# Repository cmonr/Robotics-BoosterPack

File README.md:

Robotics-BoosterPack
====================

Robotics BoosterPack for the Tiva Launchpad

For lack of a better place, the Mouser BoM: 
[Mouser BoM](http://www.mouser.com/ProjectManager/ProjectDetail.aspx?AccessID=04738dc8be)

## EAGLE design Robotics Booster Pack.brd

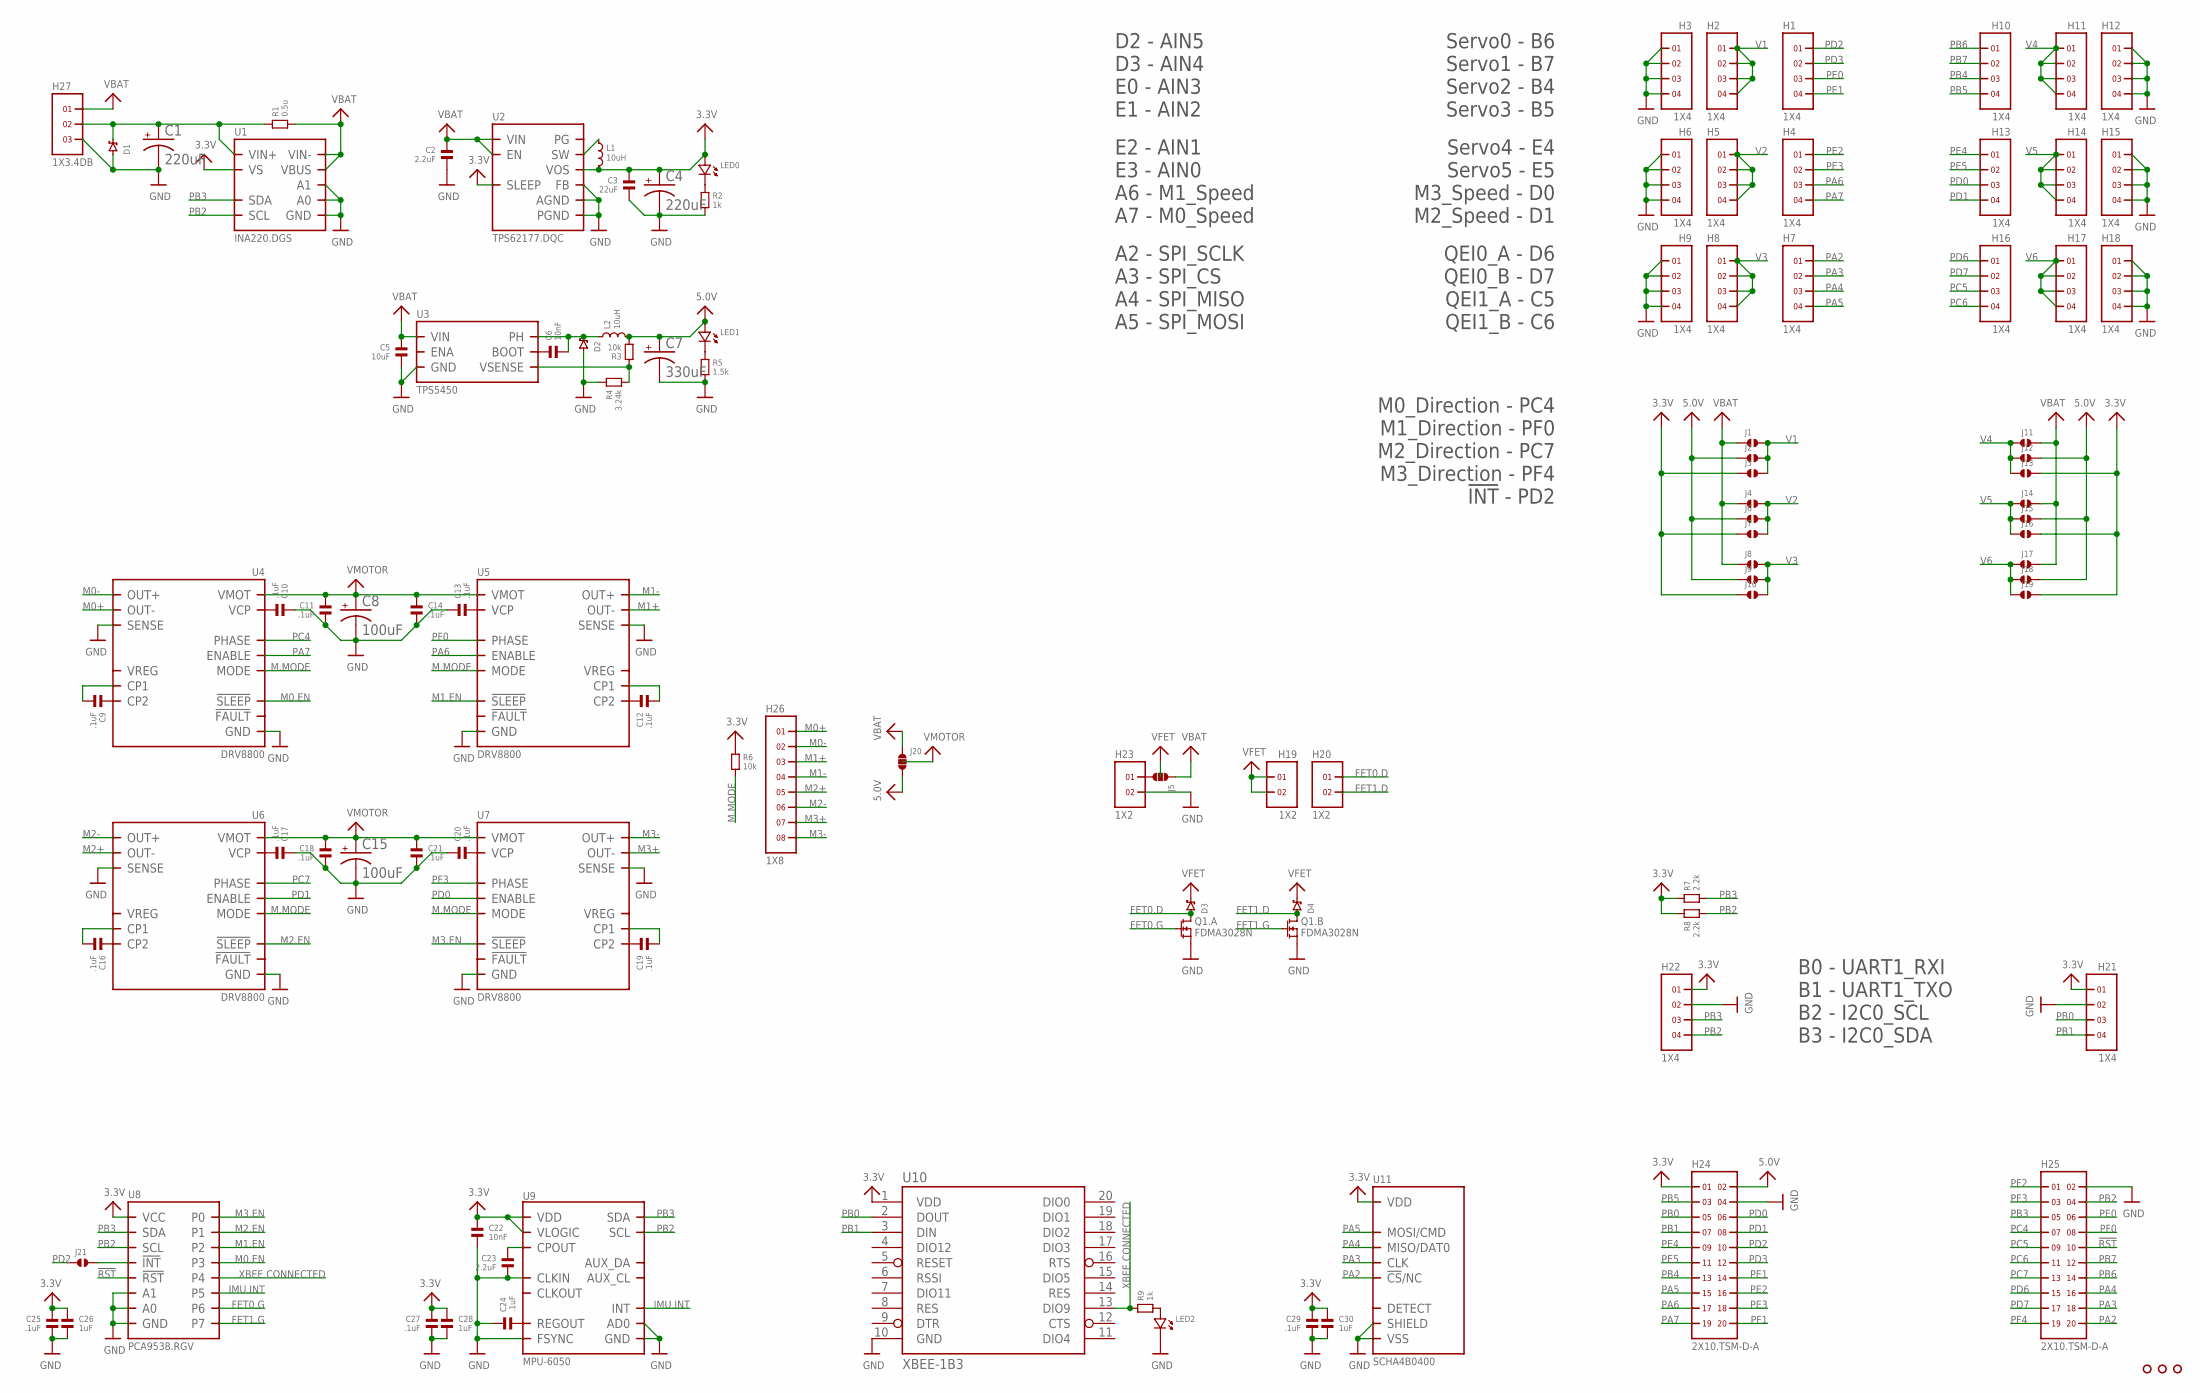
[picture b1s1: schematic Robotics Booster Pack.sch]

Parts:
C1, C4: 220uF; PANASONIC_E
C2, C23: 2.2uF; 0603
C3: 22uF; 0805
C5: 10uF; 1206
C6, C22: 10nF; 0603
C7: 330uF; PANASONIC_E
C8, C15: 100uF; PANASONIC_E
C9, C10, C11, C12, C13, C14, C16, C17, C18, C19, C20, C21, C24, C25, C27, C29: .1uF; 0603
C26, C28, C30: 1uF; 0603
D1, D3, D4: CDBMT2100-HF; SOD-123H
D2: CDBC5XXX-G; DO-214AB
H1, H2, H3, H4, H5, H6, H7, H8, H9, H10, H11, H12, H13, H14, H15, H16, H17, H18, H21, H22: 1X4
H19, H20, H23: 1X2
H24, H25: 2X10.TSM-D-A; TSM-110-XX-XXX-DV-A
H26: 1X8; 1824480000
H27: 1X3.4DB; 4DB-P108-02
J1, J2, J4, J6, J8, J9, J11, J13, J14, J15, J17, J18, J21: SOLDERJUMPER.2.LRG; 2.LRG
J3, J7, J10, J12, J16, J19: SOLDERJUMPER.2.LRG.PASTE; 2.LRG.PASTE
J5, J20: SOLDERJUMPER.3.LRG.12; 3.LRG.12
L1: 10uH; SRN6045
L2: 10uH; XAL6060
LED0, LED1, LED2: LED.0603; 0603.LED
Q1: FDMA3028N; MICROFET.2X2
R1: 0.5u; 2512
R2, R9: 1k; 0603
R3, R6: 10k; 0603
R4: 3.24k; 0603
R5: 1.5k; 0603
R7, R8: 2.2k; 0603
U1: INA220.DGS; DGS.10
U2: TPS62177.DQC; DQC
U3: TPS5450; DDA
U4, U5, U6, U7: DRV8800; RTY.16
U8: PCA9538.RGV; RGV.16
U9: MPU-6050; QFN.24.4X4
U10: XBEE-1B3; XBEE-SMD
U11: SCHA4B0400
U$3, U$4, U$21: HOLE.4MM; #4

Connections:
3.3V: C3.1, C4.+, C22.1, C25.1, C26.1, C27.1, C28.1, C29.1, C30.1, H21.1, H22.1, H24.1, J3.1, J7.1, J10.1, J13.1, J16.1, J19.1, L1.2, LED0.P$1 (1), R6.1, R7.1, R8.1, U1.6 (VS), U2.8 (SLEEP), U2.10 (VOS), U8.14 (VCC), U9.8 (VLOGIC), U9.13 (VDD), U10.1 (VDD), U11.VDD
5.0V: C7.+, H24.2, J2.1, J6.1, J9.1, J12.1, J15.1, J18.1, J20.3, L2.2, LED1.P$1 (1), R3.2
!RST: H25.10, U8.1 (!RST)
FET0.D: D3.2, H20.1, Q1.6 (D), Q1.PAD@1 (D)
FET0.G: Q1.2 (G), U8.9 (P6)
FET1.D: D4.2, H20.2, Q1.3 (D), Q1.PAD@2 (D)
FET1.G: Q1.5 (G), U8.10 (P7)
GND: C1.-, C2.2, C3.2, C4.-, C5.2, C7.-, C8.-, C10.1, C11.2, C13.1, C14.2, C15.-, C17.1, C18.2, C20.1, C21.2, C22.2, C23.2, C24.1, C25.2, C26.2, C27.2, C28.2, C29.2, C30.2, D1.2, D2.2, H3.1, H3.2, H3.3, H3.4, H6.1, H6.2, H6.3, H6.4, H9.1, H9.2, H9.3, H9.4, H12.1, H12.2, H12.3, H12.4, H15.1, H15.2, H15.3, H15.4, H18.1, H18.2, H18.3, H18.4, H21.2, H22.2, H23.2, H24.4, H25.2, H27.3, LED2.P$2 (2), Q1.1 (S), Q1.4 (S), R2.2, R4.1, R5.2, U1.1 (A1), U1.2 (A0), U1.7 (GND), U2.1 (PGND), U2.5 (FB), U2.6 (AGND), U2.PAD (PGND), U3.6 (GND), U3.PAD (GND), U4.2 (GND), U4.7 (SENSE), U4.12 (GND), U4.PAD (GND), U5.2 (GND), U5.7 (SENSE), U5.12 (GND), U5.PAD (GND), U6.2 (GND), U6.7 (SENSE), U6.12 (GND), U6.PAD (GND), U7.2 (GND), U7.7 (SENSE), U7.12 (GND), U7.PAD (GND), U8.6 (GND), U8.15 (A0), U8.16 (A1), U8.PAD (GND), U9.1 (CLKIN), U9.9 (AD0), U9.11 (FSYNC), U9.18 (GND), U10.10 (GND), U11.GND (VSS), U11.GND@1 (VSS), U11.GND@2 (VSS), U11.SHIELD, U11.SHIELD@1 (SHIELD), U11.SHIELD@2 (SHIELD), U11.SHIELD@3 (SHIELD), U11.VSS
IMU.INT: U8.8 (P5), U9.12 (INT)
M0+: H26.1@1 (1), H26.1@2 (1), U4.9 (OUT-)
M0-: H26.2@1 (2), H26.2@2 (2), U4.6 (OUT+)
M0.EN: U4.3 (!SLEEP), U8.5 (P3)
M1+: H26.3@1 (3), H26.3@2 (3), U5.9 (OUT-)
M1-: H26.4@1 (4), H26.4@2 (4), U5.6 (OUT+)
M1.EN: U5.3 (!SLEEP), U8.4 (P2)
M2+: H26.5@1 (5), H26.5@2 (5), U6.9 (OUT-)
M2-: H26.6@1 (6), H26.6@2 (6), U6.6 (OUT+)
M2.EN: U6.3 (!SLEEP), U8.3 (P1)
M3+: H26.7@1 (7), H26.7@2 (7), U7.9 (OUT-)
M3-: H26.8@1 (8), H26.8@2 (8), U7.6 (OUT+)
M3.EN: U7.3 (!SLEEP), U8.2 (P0)
M.MODE: R6.2, U4.16 (MODE), U5.16 (MODE), U6.16 (MODE), U7.16 (MODE)
unnamed: L1.1, U2.9 (SW)
unnamed: LED0.P$2 (2), R2.1
unnamed: LED1.P$2 (2), R5.1
unnamed: LED2.P$1 (1), R9.2
unnamed: H23.1, J5.3
unnamed: C24.2, U9.10 (REGOUT)
unnamed: J21.2, U8.11 (!INT)
unnamed: C9.1, U4.11 (CP2)
unnamed: C10.2, U4.13 (VCP)
unnamed: C13.2, U5.13 (VCP)
unnamed: C17.2, U6.13 (VCP)
unnamed: C20.2, U7.13 (VCP)
unnamed: C1.+, D1.1, H27.2, R1.1, U1.10 (VIN+)
unnamed: C23.1, U9.20 (CPOUT)
unnamed: C12.1, U5.11 (CP2)
unnamed: C16.1, U6.11 (CP2)
unnamed: C19.1, U7.11 (CP2)
unnamed: C6.1, U3.1 (BOOT)
unnamed: C6.2, D2.1, L2.1, U3.8 (PH)
unnamed: R3.1, R4.2, U3.4 (VSENSE)
unnamed: C16.2, U6.10 (CP1)
unnamed: C9.2, U4.10 (CP1)
unnamed: C12.2, U5.10 (CP1)
unnamed: C19.2, U7.10 (CP1)
PA2: H7.1, H25.20, U11.!CS!/NC/DAT3 (!CS!/NC)
PA3: H7.2, H25.18, U11.CLK
PA4: H7.3, H25.16, U11.MISO/DAT0
PA5: H7.4, H24.15, U11.MOSI/CMD
PA6: H4.3, H24.17, U5.4 (ENABLE)
PA7: H4.4, H24.19, U4.4 (ENABLE)
PB0: H21.3, H24.5, U10.2 (DOUT)
PB1: H21.4, H24.7, U10.3 (DIN)
PB2: H22.4, H25.4, R8.2, U1.5 (SCL), U8.12 (SCL), U9.23 (SCL)
PB3: H22.3, H25.5, R7.2, U1.4 (SDA), U8.13 (SDA), U9.24 (SDA)
PB4: H10.3, H24.13
PB5: H10.4, H24.3
PB6: H10.1, H25.14
PB7: H10.2, H25.12
PC4: H25.7, U4.1 (PHASE)
PC5: H16.3, H25.9
PC6: H16.4, H25.11
PC7: H25.13, U6.1 (PHASE)
PD0: H13.3, H24.6, U7.4 (ENABLE)
PD1: H13.4, H24.8, U6.4 (ENABLE)
PD2: H1.1, H24.10, J21.1
PD3: H1.2, H24.12
PD6: H16.1, H25.15
PD7: H16.2, H25.17
PE0: H1.3, H25.6
PE1: H1.4, H24.14
PE2: H4.1, H24.16
PE3: H4.2, H24.18
PE4: H13.1, H24.9
PE5: H13.2, H24.11
PF0: H25.8, U5.1 (PHASE)
PF1: H24.20
PF2: H25.1
PF3: H25.3, U7.1 (PHASE)
PF4: H25.19
V1: H2.1, H2.2, H2.3, H2.4, J1.2, J2.2, J3.2
V2: H5.1, H5.2, H5.3, H5.4, J4.2, J6.2, J7.2
V3: H8.1, H8.2, H8.3, H8.4, J8.2, J9.2, J10.2
V4: H11.1, H11.2, H11.3, H11.4, J11.2, J12.2, J13.2
V5: H14.1, H14.2, H14.3, H14.4, J14.2, J15.2, J16.2
V6: H17.1, H17.2, H17.3, H17.4, J17.2, J18.2, J19.2
VBAT: C2.1, C5.1, H27.1, J1.1, J4.1, J5.1, J8.1, J11.1, J14.1, J17.1, J20.1, R1.2, U1.8 (VBUS), U1.9 (VIN-), U2.2 (VIN), U2.3 (EN), U3.7 (VIN)
VFET: D3.1, D4.1, H19.1, H19.2, J5.2
VMOTOR: C8.+, C11.1, C14.1, C15.+, C18.1, C21.1, J20.2, U4.8 (VMOT), U5.8 (VMOT), U6.8 (VMOT), U7.8 (VMOT)
XBEE.CONNECTED: R9.1, U8.7 (P4), U10.13 (DIO9)

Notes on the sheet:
D2 - AIN5 D3 - AIN4 E0 - AIN3 E1 - AIN2
E2 - AIN1 E3 - AIN0 A6 - M1_Speed A7 - M0_Speed
A2 - SPI_SCLK A3 - SPI_CS A4 - SPI_MISO A5 - SPI_MOSI
Servo0 - B6 Servo1 - B7 Servo2 - B4 Servo3 - B5
Servo4 - E4 Servo5 - E5 M3_Speed - D0 M2_Speed - D1
QEI0_A - D6 QEI0_B - D7 QEI1_A - C5 QEI1_B - C6
B0 - UART1_RXI B1 - UART1_TXO B2 - I2C0_SCL B3 - I2C0_SDA
M0_Direction - PC4 M1_Direction - PF0 M2_Direction - PC7 M3_Direction - PF4 !INT! - PD2

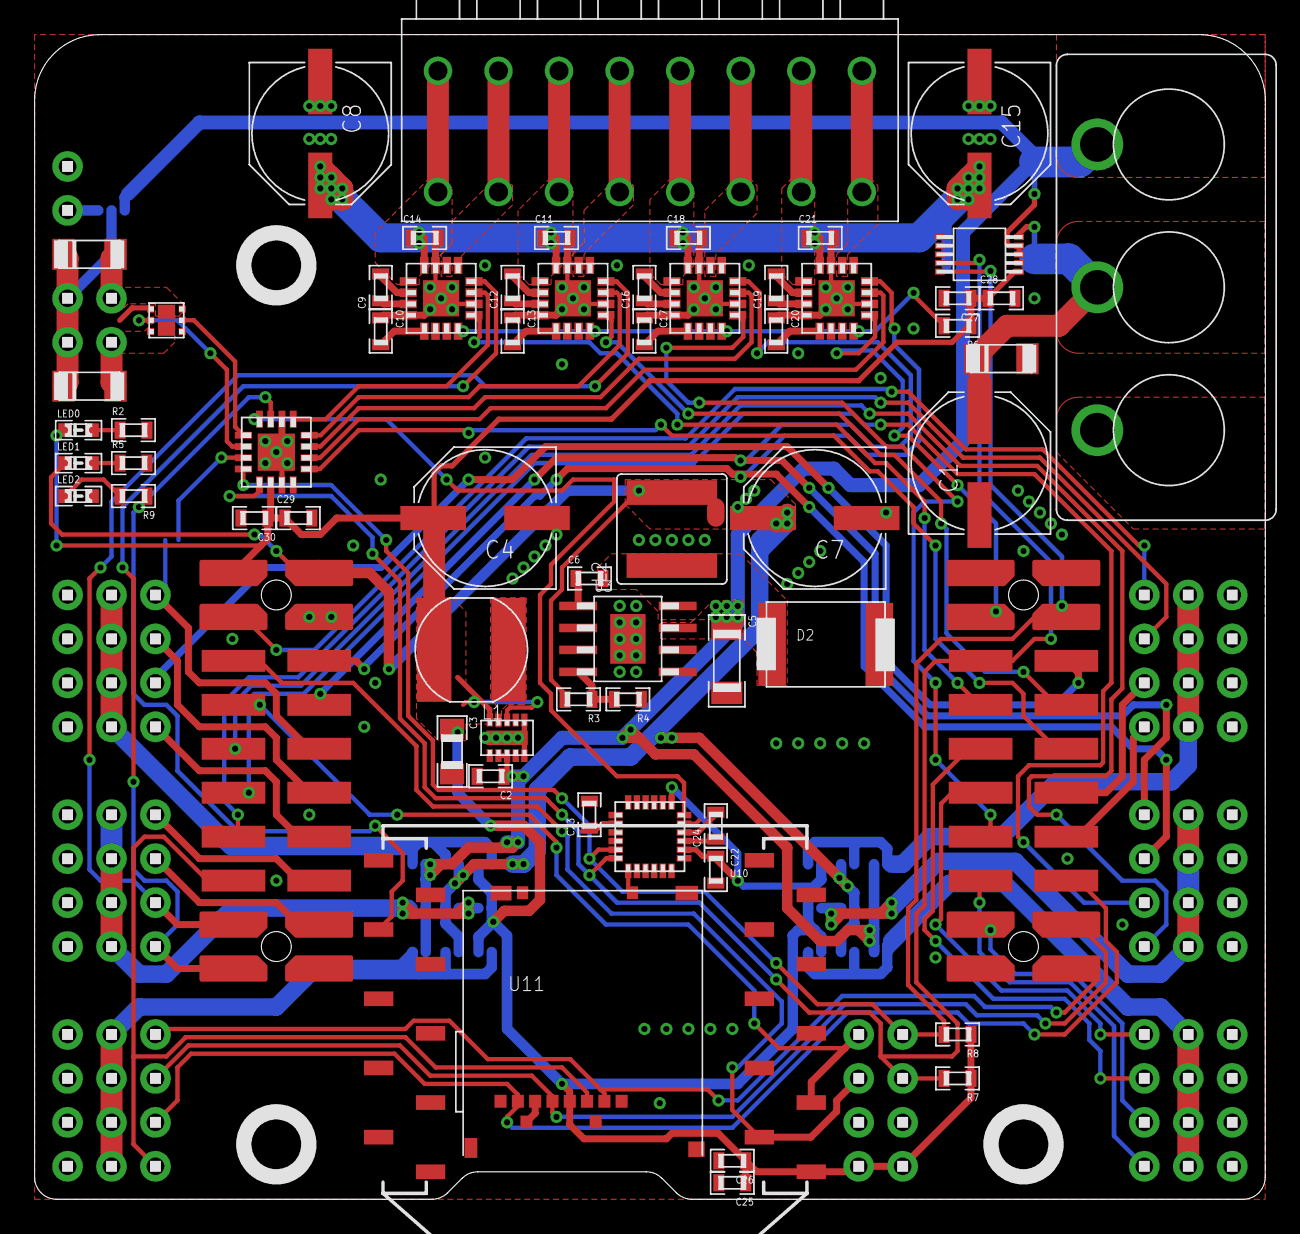
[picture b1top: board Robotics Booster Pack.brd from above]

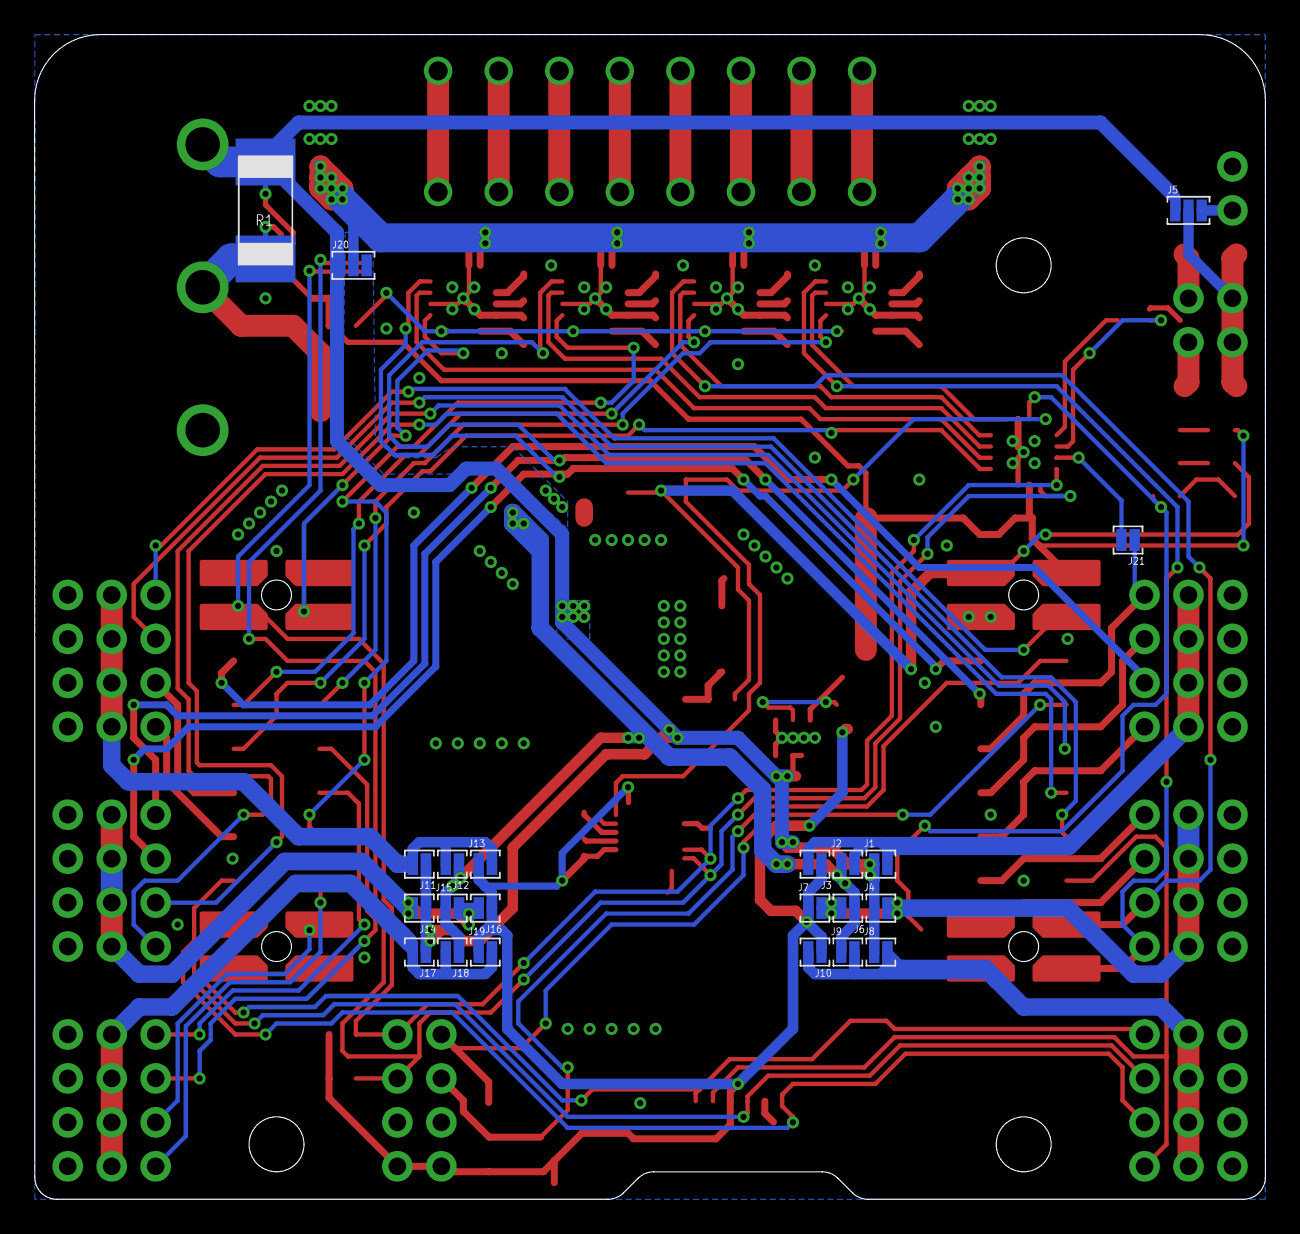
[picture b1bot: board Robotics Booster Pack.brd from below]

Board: 2 copper layers, 71.1 x 67.3 mm, 111 parts (22 on the bottom side), 88 nets.

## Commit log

2013-05-02 Organizing folders into subdirectories for upcoming projects
2013-05-03 Renamed files. Corrected uSD Card package. All other ICs check out.
2013-08-01 Creating base board for Pololu Black Motor Mount
2013-08-08 Generated updated images for Robotics Booster Pack
2013-08-11 Addressed all issues in github repo Moved GPIO & Mosfet connections up because of USB connector in Launchpad Fixed SPI pin swap Added diode between 5v and VBUS Changed jumpers for UART BT/XBee select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
2013-08-13 Created AS5035 FLoating Encoder
2013-08-13 Changed Pinouts of BoosterPack * SPI Encoders replaced with QEI * SD Card/SPI interface moved to port F * Motor Control Signals moved to port A
    Layout still needs to be redone...
2013-08-17 Updated board and schematic previews
2013-08-26 Removed projects that I'm unlikely to ever get to again.
2013-08-26 Updated Board Preview
2013-09-10 Started routing v2. And by started, I mean rerouting _everything_
    ... The heck's wrong with me ...
2013-09-15 Making progress on PCB re-layout. Moved some pins around to make routing _much_ easier, along with the added improvements.
2013-10-06 Replaced 5v regulator circuit with TPS5450 Added more power options in the form of SMD Jumpers Added IO Expander-controlled Servo FET Swapped positions of XBee and extra IO/FETs to make routing simpl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
2013-10-24 Modifed Robotics BP regulators, along with a few other things
2013-10-25 Cleaned up Servo.EN connections and indicator LEDs Routing will soon begin. It's unreasonable to believe that it will all be complete by the end of the weekend, bu some goals aren't meant to be met.
2013-10-26 Began routing of Robotics BP v2 Bluetooth, XBee, and UART mux routing nearly complete. Started LEDs and IMU routing.
2013-11-04 More Robotics BP v2 routing. Power regulators routed and completed Most IO Expander signals completely routed
2013-11-05 More Routing for Robotics Booster Pack v2. Assuming UART0 header is oriented correctly, the top 25% of board is completely routed!
2013-11-07 Even more routing! With any luck, all routing will be completed by the end of tomorrow ^^;
2013-11-08 Robotics BoosterPack v2 Complete! Still need to double check a few mote things, and clean up the silkscreen.
2013-11-08 Cleaned up completed Robotics Booster Pack v2. Sent off to OSHPark!
2013-11-27 Cleaned up part names
2014-04-12 Began starting on v2.1 Removed: Bluetooth Module, Servo Enable IC, Buffer IC. Corrected Motor PWM/IO signals issue Centered power ICs
2014-05-07 Let the carnage that shall be known as v3 begin!
2014-05-08 Continued working on RBP v3 Using TPS62177 for 3.3v regulator circuit, new Vin headers, moving things around.
2014-05-09 COntinuing work on RBP v3 Added smd headers to replace Launchpad throguh hole headers (more routing space on the bottom) Moved around motor controllers -n- stuff.
2014-05-10 Continuing RBP v3 rerouting. Figured out desired placement of headers. Thinking of adding FET to control power going out of board (NTMFS4897NFT1G). Need to replace IO expander; might need 16 pins ins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
2014-05-11 Got everything mostly figured out as to where I want things. Using larger capacitors. Pin header mappings decided on. Routing will be hell... Still need to figure out how to distribute all power vari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
2014-05-11 Part placement ~90% completed. Started routing. Pin mapping figured out (for the most part).
2014-05-11 Updated images.
2014-05-11 Part placement is mostly complete for RBP v3. Layout coming along. Routing multiple Power Header Options will be difficult...
2014-05-12 More routing. Completed Motor Controller power traces and 3.3v & 5v regulator power traces.
2014-05-14 More routing fun! Got a significant amount ofpower signals rounted. Replaced 1W 1mOhm power resistor with 3W 0.5mOhm resistor (able to carry much more current)
2014-05-17 Board completely routed! Silkscreen needed, and final mulling/triple check needed, but otherwise, it's nearly ready to be made!
2014-05-17 Robitcs BPv3 cleaned up, with silkscreen added. Ready to be fabricated!
2014-05-25 Removed .csv file for now
2014-05-25 Also removed .dxf (leftover from gerber generation?)
2014-05-28 Exported BoM. Moved around schematic and renamed parts to be contiguous
2014-05-28 Added link to Mouser BoM
2014-06-07 Added .dxf export for stencil

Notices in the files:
parts and their libraries:
SparkFun-RF: Licensing: CC v3.0 Share-Alike You are welcome to use this library for commercial purposes.
microbuilder: This work is placed in the public domain, and may be freely used for commercial and non-commercial work with the following conditions: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
